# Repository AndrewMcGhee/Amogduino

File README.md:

# Sleepduino
 ATMEGA328P Based Board

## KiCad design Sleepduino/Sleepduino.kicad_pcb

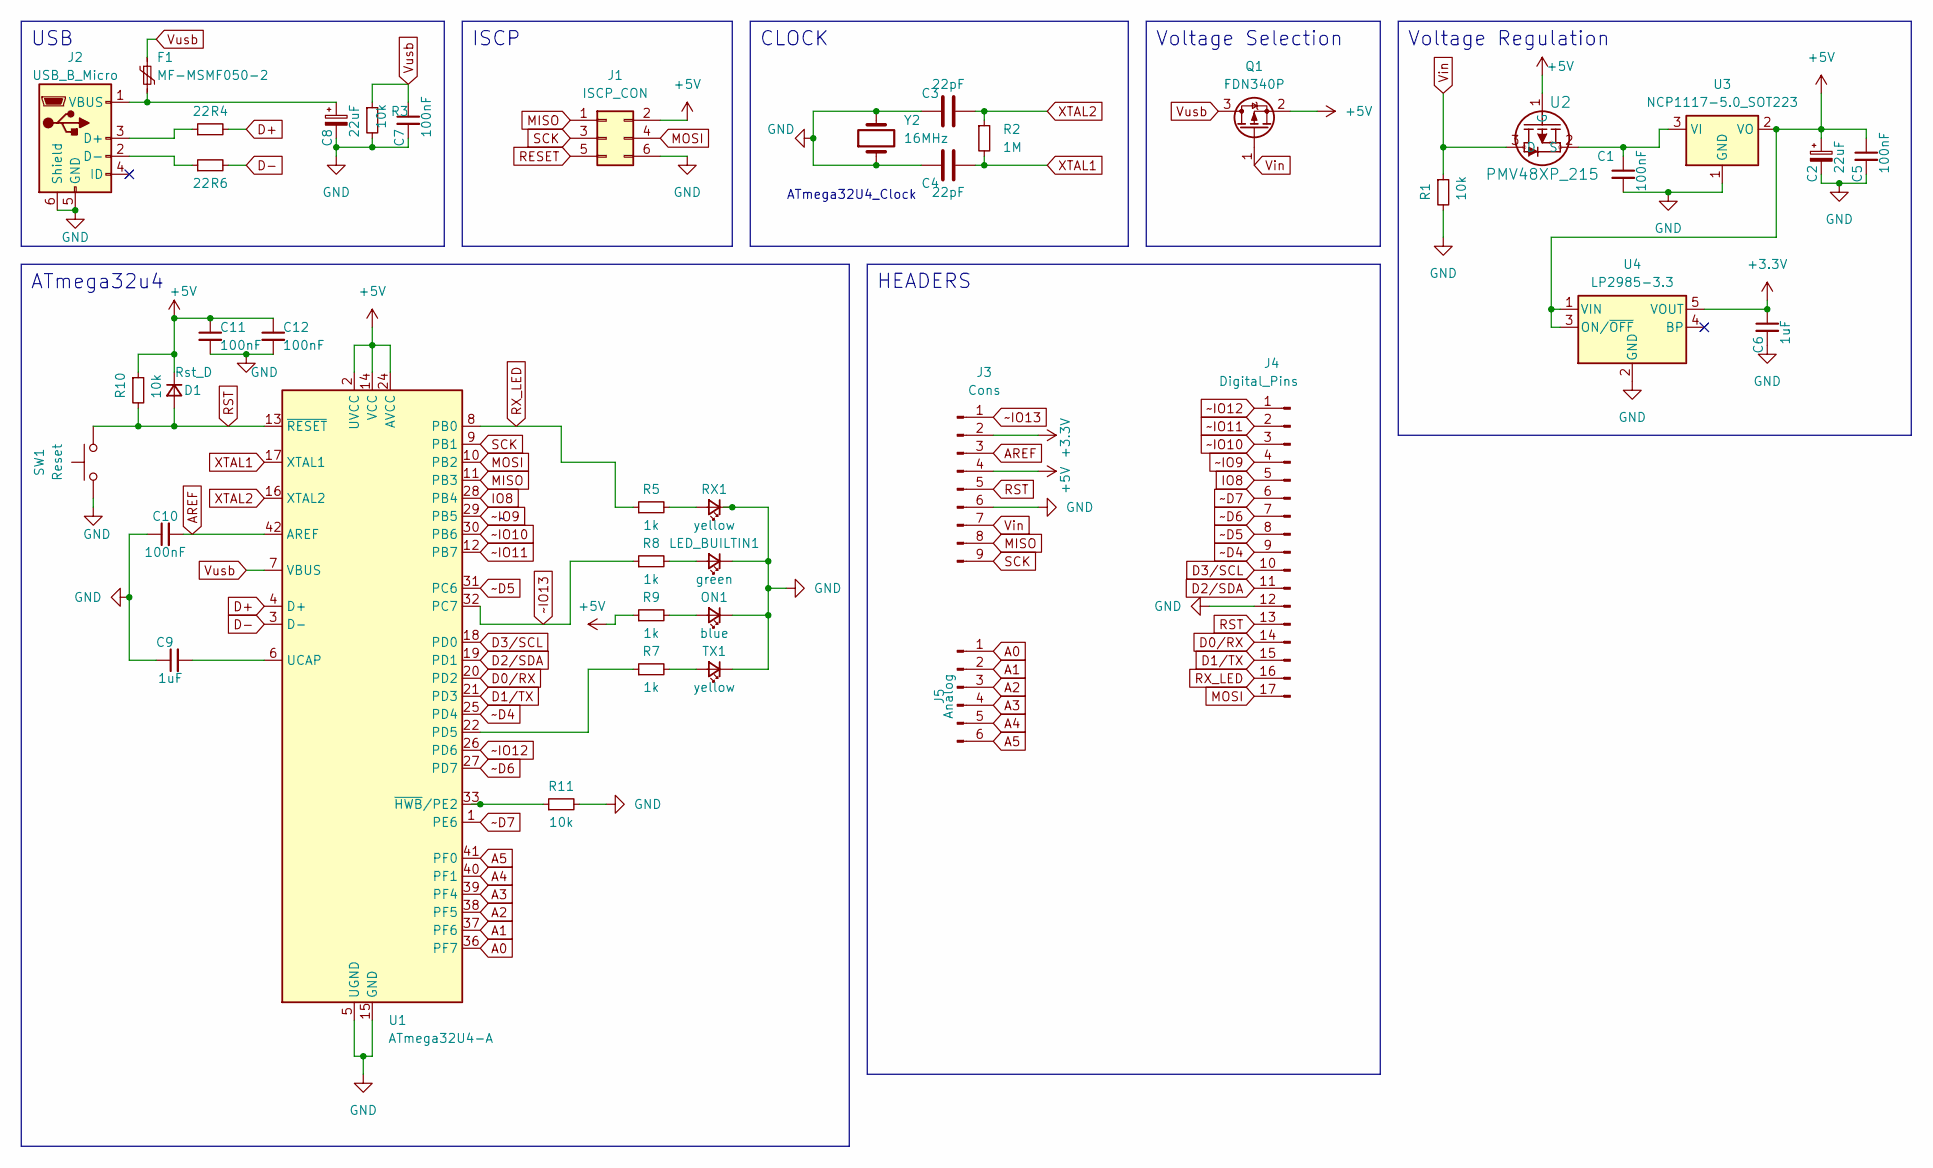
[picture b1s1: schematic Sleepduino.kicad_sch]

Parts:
C1, C5, C7, C10, C11, C12: 100nF; C_0402_1005Metric
C2, C8: 22uF; C_0402_1005Metric
C3, C4: 22pF; C_0402_1005Metric
C6, C9: 1uF; C_0402_1005Metric
D1: Rst_D; D_SOD-323
F1: MF-MSMF050-2; Fuse_1812_4532Metric
J1: ISCP_CON; PinHeader_2x03_P2.54mm_Vertical
J2: USB_B_Micro; USB_Micro-B_Molex-105017-0001
J3: Cons; PinHeader_1x09_P2.54mm_Vertical
J4: Digital_Pins; PinHeader_1x17_P2.54mm_Vertical
J5: Analog; PinHeader_1x06_P2.54mm_Vertical
LED_BUILTIN1: green; LED_0603_1608Metric
ON1: blue; LED_0603_1608Metric
Q1: FDN340P; SOT-23
R1, R3, R10, R11: 10k; R_0402_1005Metric
R2: 1M; R_0402_1005Metric
R4, R6: 22; R_0402_1005Metric
R5, R7, R8, R9: 1k; R_0402_1005Metric
RX1: yellow; LED_0603_1608Metric
SW1: Reset; SW_SPST_TL3342
TX1: yellow; LED_0603_1608Metric
U1: ATmega32U4-A; TQFP-44_10x10mm_P0.8mm
U2: PMV48XP_215; TO-236_SOT23_NEX
U3: NCP1117-5.0_SOT223; SOT-223-3_TabPin2
U4: LP2985-3.3; SOT-23-5
Y2: 16MHz; Crystal_HC49-4H_Vertical

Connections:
+3.3V: C6.1, J3.2, U4.5 (VOUT)
+5V: C2.1, C5.1, C11.1, C12.1, D1.1 (K), J1.2, J3.4, Q1.2 (S), R9.1, R10.1, U1.2 (UVCC), U1.14 (VCC), U1.24 (AVCC), U1.34 (VCC), U1.44 (AVCC), U2.1 (G), U3.2 (VO), U4.1 (VIN), U4.3 (ON/~OFF)
A0: J5.1, U1.36 (PF7)
A1: J5.2, U1.37 (PF6)
A2: J5.3, U1.38 (PF5)
A3: J5.4, U1.39 (PF4)
A4: J5.5, U1.40 (PF1)
A5: J5.6, U1.41 (PF0)
AREF: C10.2, J3.3, U1.42 (AREF)
D0/RX: J4.14, U1.20 (PD2)
D1/TX: J4.15, U1.21 (PD3)
D2/SDA: J4.11, U1.19 (PD1)
D3/SCL: J4.10, U1.18 (PD0)
D+: R4.2, U1.4 (D+)
D-: R6.2, U1.3 (D-)
GND: C1.2, C2.2, C3.1, C4.1, C5.2, C6.2, C7.2, C8.2, C9.1, C10.1, C11.2, C12.2, J1.6, J2.5 (GND), J2.6 (Shield), J3.6, J4.12, LED_BUILTIN1.1 (K), ON1.1 (K), R1.2, R3.2, R11.2, RX1.1 (K), SW1.1, TX1.1 (K), U1.5 (UGND), U1.15 (GND), U1.23 (GND), U1.35 (GND), U1.43 (GND), U3.1 (GND), U4.2 (GND), Y2.1, Y2.2
IO8: J4.5, U1.28 (PB4)
MISO: J1.1, J3.8, U1.11 (PB3)
MOSI: J1.4, J4.17, U1.10 (PB2)
unnamed: J2.3 (D+), R4.1
unnamed: J2.2 (D-), R6.1
unnamed: C8.1, F1.2, J2.1 (VBUS)
unnamed: LED_BUILTIN1.2 (A), R8.2
unnamed: ON1.2 (A), R9.2
unnamed: R5.2, RX1.2 (A)
unnamed: R7.2, TX1.2 (A)
unnamed: R7.1, U1.22 (PD5)
unnamed: C9.2, U1.6 (UCAP)
unnamed: R11.1, U1.33 (~HWB/PE2)
unnamed: C1.1, U2.2 (S), U3.3 (VI)
RESET: J1.5
RST: D1.2 (A), J3.5, J4.13, R10.2, SW1.2, U1.13 (~RESET)
RX_LED: J4.16, R5.1, U1.8 (PB0)
SCK: J1.3, J3.9, U1.9 (PB1)
Vin: J3.7, Q1.1 (G), R1.1, U2.3 (D)
Vusb: C7.1, F1.1, Q1.3 (D), R3.1, U1.7 (VBUS)
XTAL1: C4.2, R2.2, U1.17 (XTAL1)
XTAL2: C3.2, R2.1, U1.16 (XTAL2)
~D4: J4.9, U1.25 (PD4)
~D5: J4.8, U1.31 (PC6)
~D6: J4.7, U1.27 (PD7)
~D7: J4.6, U1.1 (PE6)
~IO9: J4.4, U1.29 (PB5)
~IO10: J4.3, U1.30 (PB6)
~IO11: J4.2, U1.12 (PB7)
~IO12: J4.1, U1.26 (PD6)
~IO13: J3.1, R8.1, U1.32 (PC7)

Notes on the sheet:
Voltage Selection
Voltage Regulation
ATmega32u4
HEADERS
ATmega32U4_Clock
CLOCK
ISCP
USB

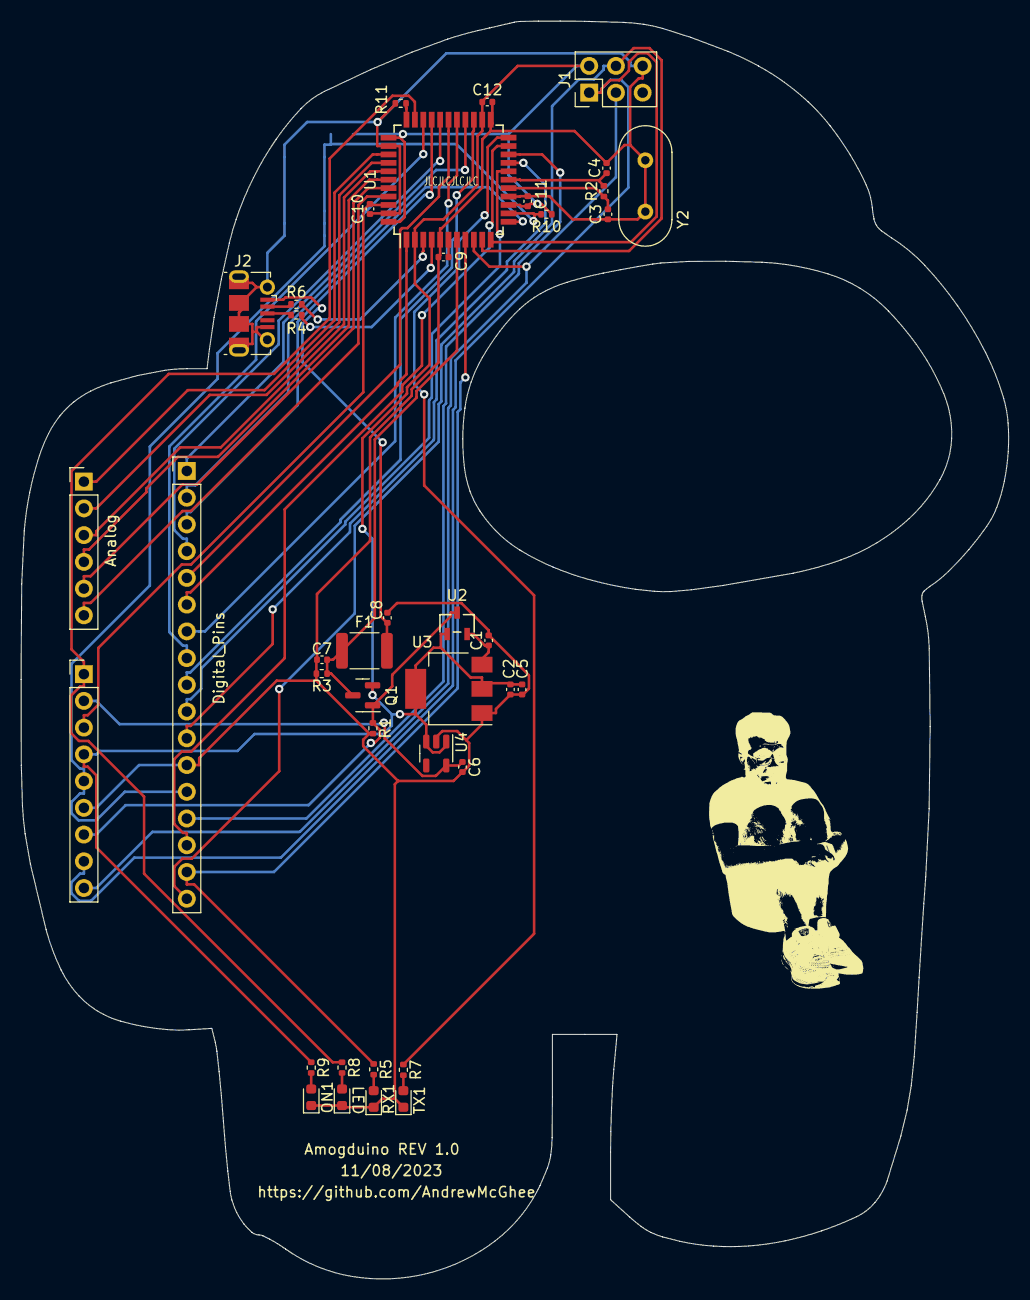
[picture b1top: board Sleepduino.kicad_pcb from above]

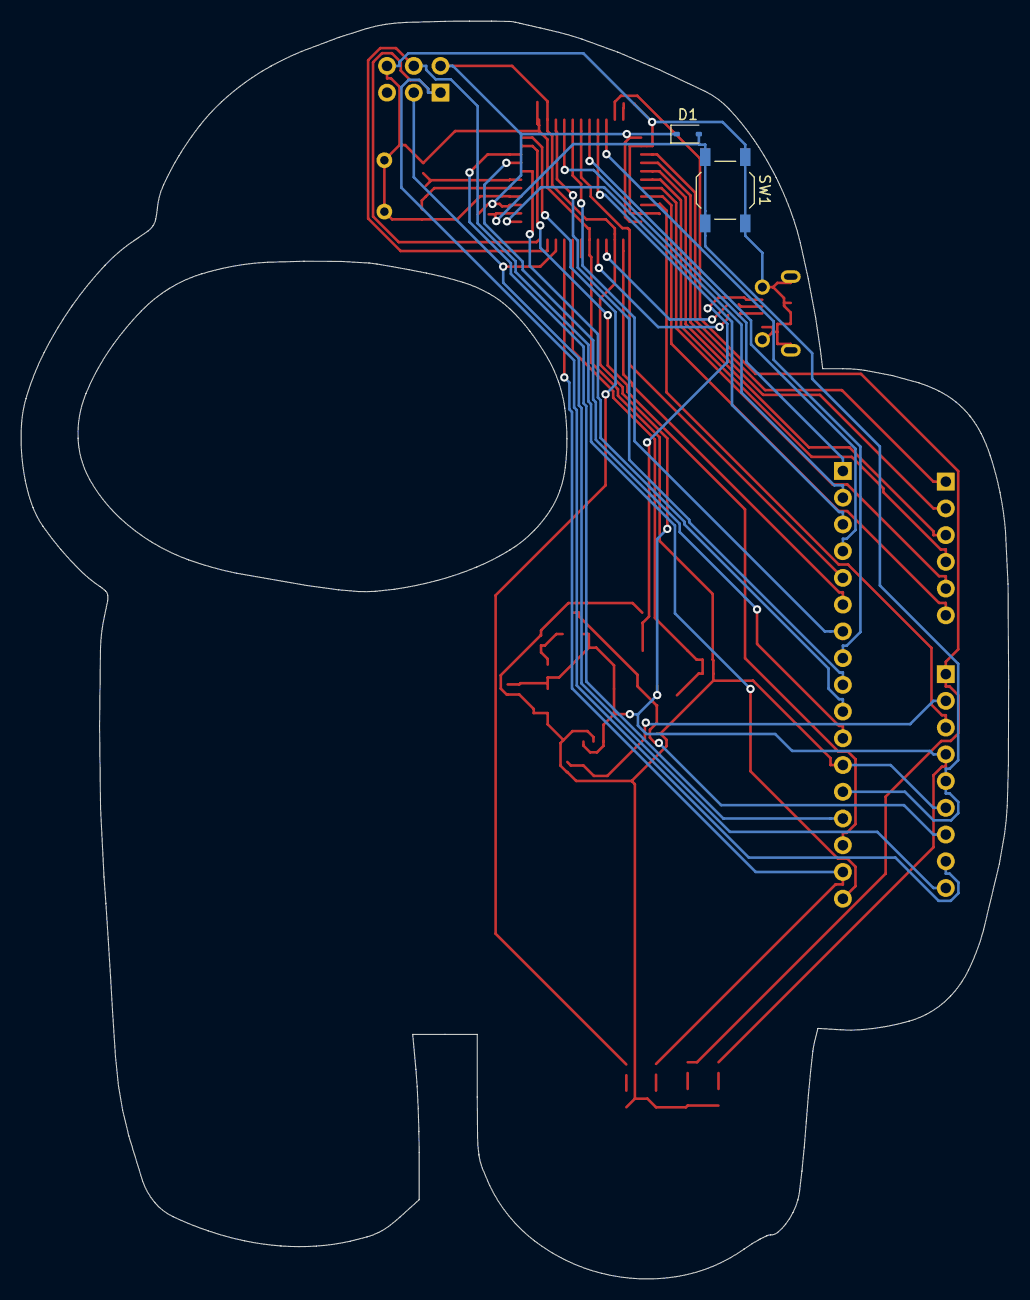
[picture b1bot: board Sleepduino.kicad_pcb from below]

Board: 2 copper layers, 93.8 x 119.5 mm, 41 parts (2 on the bottom side), 46 nets.

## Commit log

2023-11-02 progress
2023-11-08 massive gains
